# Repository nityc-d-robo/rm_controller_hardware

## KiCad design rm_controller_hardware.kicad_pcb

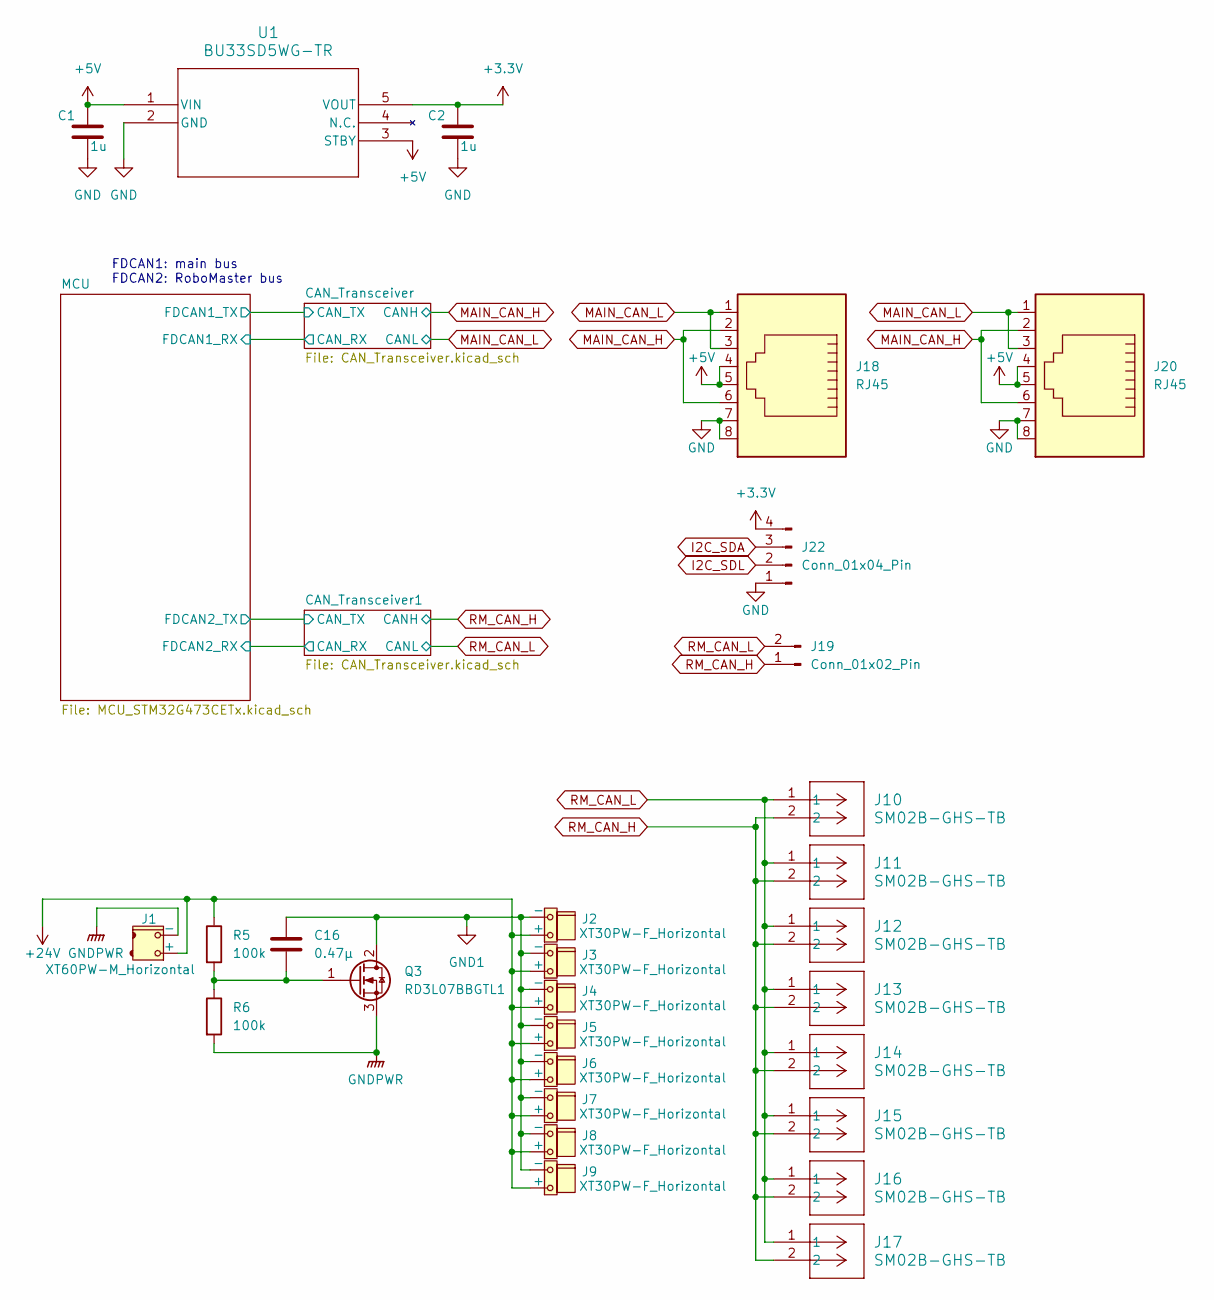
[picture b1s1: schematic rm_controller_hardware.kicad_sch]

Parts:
C1, C2: 1u; C_0603_1608Metric
C16: 0.47μ; C_0603_1608Metric_Pad1.08x0.95mm_HandSolder
J1: XT60PW-M_Horizontal; AMASS_XT60PW-M_1x02_P7.20mm_Horizontal
J2, J3, J4, J5, J6, J7, J8, J9: XT30PW-F_Horizontal; AMASS_XT30PW-F_1x02_P2.50mm_Horizontal
J10, J11, J12, J13, J14, J15, J16, J17: SM02B-GHS-TB; JST_GH_SM02B-GHS-TB_1x02-1MP_P1.25mm_Horizontal
J18, J20: RJ45; RJ45_Amphenol_54602-x08_Horizontal
J19: Conn_01x02_Pin; JST_XH_B2B-XH-A_1x02_P2.50mm_Vertical
J22: Conn_01x04_Pin; JST_XH_S4B-XH-A_1x04_P2.50mm_Horizontal
Q3: RD3L07BBGTL1; TO252-3_ROM
R5, R6: 100k; R_0603_1608Metric_Pad0.98x0.95mm_HandSolder
U1: BU33SD5WG-TR; SSOP5_ROM

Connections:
+5V: C1.1, J18.4, J18.5, J20.4, J20.5, U1.1 (VIN), U1.3 (STBY); also elsewhere on the board
+24V: J1.2 (+), J2.2 (+), J3.2 (+), J4.2 (+), J5.2 (+), J6.2 (+), J7.2 (+), J8.2 (+), J9.2 (+), R5.1
GND1: C16.1, J2.1 (-), J3.1 (-), J4.1 (-), J5.1 (-), J6.1 (-), J7.1 (-), J8.1 (-), J9.1 (-), Q3.2 (D)
GNDPWR: J1.1 (-), Q3.3 (S), R6.2
I2C_SDA: J22.3; also elsewhere on the board
I2C_SDL: J22.2; also elsewhere on the board
MAIN_CAN_H: J18.2, J18.6, J20.2, J20.6; also elsewhere on the board
MAIN_CAN_L: J18.1, J18.3, J20.1, J20.3; also elsewhere on the board
unnamed: C16.2, Q3.1 (G), R5.2, R6.1
RM_CAN_H: J10.2, J11.2, J12.2, J13.2, J14.2, J15.2, J16.2, J17.2, J19.1; also elsewhere on the board
RM_CAN_L: J10.1, J11.1, J12.1, J13.1, J14.1, J15.1, J16.1, J17.1, J19.2; also elsewhere on the board
VDD: C2.1, J22.4, U1.5 (VOUT); also elsewhere on the board
VSS: C1.2, C2.2, J18.7, J18.8, J20.7, J20.8, J22.1, U1.2 (GND); also elsewhere on the board

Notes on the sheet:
FDCAN1: main bus FDCAN2: RoboMaster bus

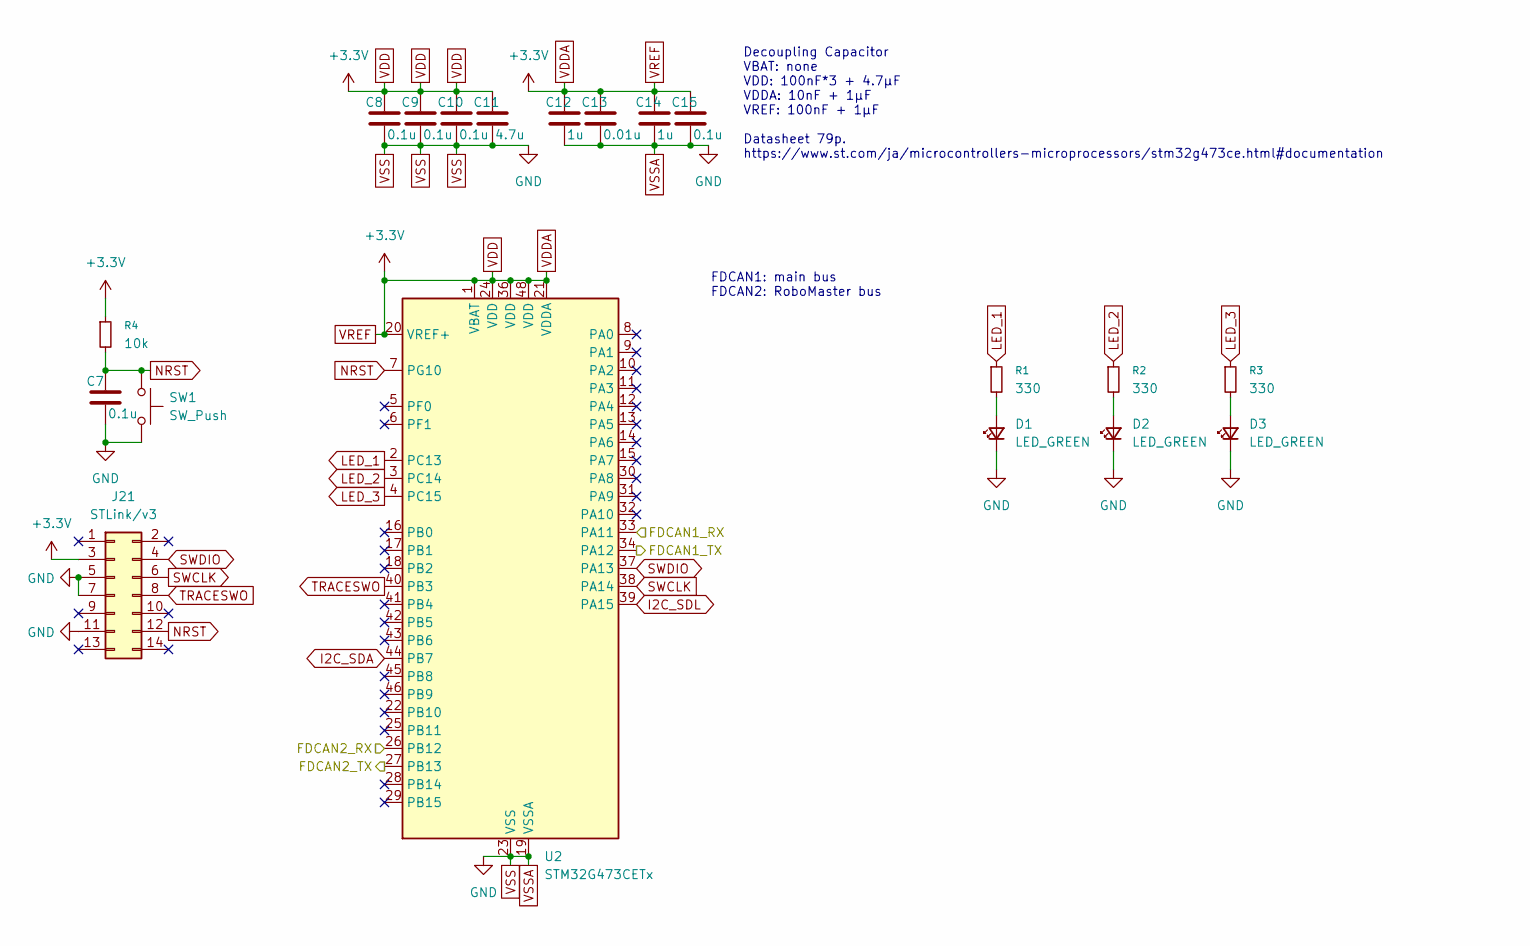
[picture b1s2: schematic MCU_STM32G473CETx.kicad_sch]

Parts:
C7, C8, C9, C10, C15: 0.1u; C_0603_1608Metric
C11: 4.7u; C_0603_1608Metric
C12, C14: 1u; C_0603_1608Metric
C13: 0.01u; C_0603_1608Metric
D1, D2, D3: LED_GREEN; LED_0603_1608Metric_Pad1.05x0.95mm_HandSolder
J21: STLink/v3; CONN14_3220-14_CNC
R1, R2, R3: 330; R_0603_1608Metric_Pad0.98x0.95mm_HandSolder
R4: 10k; R_0603_1608Metric_Pad0.98x0.95mm_HandSolder
SW1: SW_Push; TVAF06-A020B-R
U2: STM32G473CETx; LQFP-48_7x7mm_P0.5mm

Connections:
/CAN_Transceiver1/CAN_RX: U2.26 (PB12); also elsewhere on the board
/CAN_Transceiver1/CAN_TX: U2.27 (PB13); also elsewhere on the board
/CAN_Transceiver/CAN_RX: U2.33 (PA11); also elsewhere on the board
/CAN_Transceiver/CAN_TX: U2.34 (PA12); also elsewhere on the board
I2C_SDA: U2.44 (PB7); also elsewhere on the board
I2C_SDL: U2.39 (PA15); also elsewhere on the board
LED_1: R1.1, U2.2 (PC13)
LED_2: R2.1, U2.3 (PC14)
LED_3: R3.1, U2.4 (PC15)
NRST: C7.1, J21.12, R4.2, SW1.1, U2.7 (PG10)
unnamed: D1.2 (A), R1.2
unnamed: D2.2 (A), R2.2
unnamed: D3.2 (A), R3.2
SWCLK: J21.6, U2.38 (PA14)
SWDIO: J21.4, U2.37 (PA13)
TRACESWO: J21.8, U2.40 (PB3)
VDD: C8.1, C9.1, C10.1, C11.1, C12.1, C13.1, C14.1, C15.1, J21.3, R4.1, U2.1 (VBAT), U2.20 (VREF+), U2.21 (VDDA), U2.24 (VDD), U2.36 (VDD), U2.48 (VDD); also elsewhere on the board
VSS: C7.2, C8.2, C9.2, C10.2, C11.2, C12.2, C13.2, C14.2, C15.2, D1.1 (K), D2.1 (K), D3.1 (K), J21.5, J21.7, J21.11, SW1.2, U2.19 (VSSA), U2.23 (VSS), U2.35 (VSS), U2.47 (VSS); also elsewhere on the board

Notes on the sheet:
FDCAN1: main bus FDCAN2: RoboMaster bus
Decoupling Capacitor VBAT: none VDD: 100nF*3 + 4.7μF VDDA: 10nF + 1μF VREF: 100nF + 1μF Datasheet 79p. https://www.st.com/ja/microcontrollers-microprocessors/stm32g473ce.html#documentation

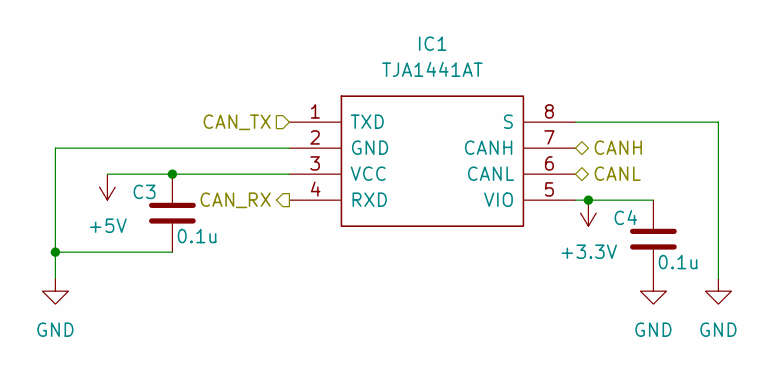
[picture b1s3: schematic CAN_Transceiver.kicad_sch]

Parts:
C3, C4: 0.1u; C_0603_1608Metric_Pad1.08x0.95mm_HandSolder
IC1: TJA1441AT; SO8_SOT96-1_NXP; Manufacturer_Part_Number TJA1441AT

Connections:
+5V: C3.1, IC1.3 (VCC); also elsewhere on the board
/CAN_Transceiver1/CAN_RX: IC1.4 (RXD); also elsewhere on the board
/CAN_Transceiver1/CAN_TX: IC1.1 (TXD); also elsewhere on the board
RM_CAN_H: IC1.7 (CANH); also elsewhere on the board
RM_CAN_L: IC1.6 (CANL); also elsewhere on the board
VDD: C4.1, IC1.5 (VIO); also elsewhere on the board
VSS: C3.2, C4.2, IC1.2 (GND), IC1.8 (S); also elsewhere on the board

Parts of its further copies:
C5, C6: 0.1u; C_0603_1608Metric_Pad1.08x0.95mm_HandSolder
IC2: TJA1441AT; SO8_SOT96-1_NXP; Manufacturer_Part_Number TJA1441AT

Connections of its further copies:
+5V: C5.1, IC2.3 (VCC); also elsewhere on the board
/CAN_Transceiver/CAN_RX: IC2.4 (RXD); also elsewhere on the board
/CAN_Transceiver/CAN_TX: IC2.1 (TXD); also elsewhere on the board
MAIN_CAN_H: IC2.7 (CANH); also elsewhere on the board
MAIN_CAN_L: IC2.6 (CANL); also elsewhere on the board
VDD: C6.1, IC2.5 (VIO); also elsewhere on the board
VSS: C5.2, C6.2, IC2.2 (GND), IC2.8 (S); also elsewhere on the board

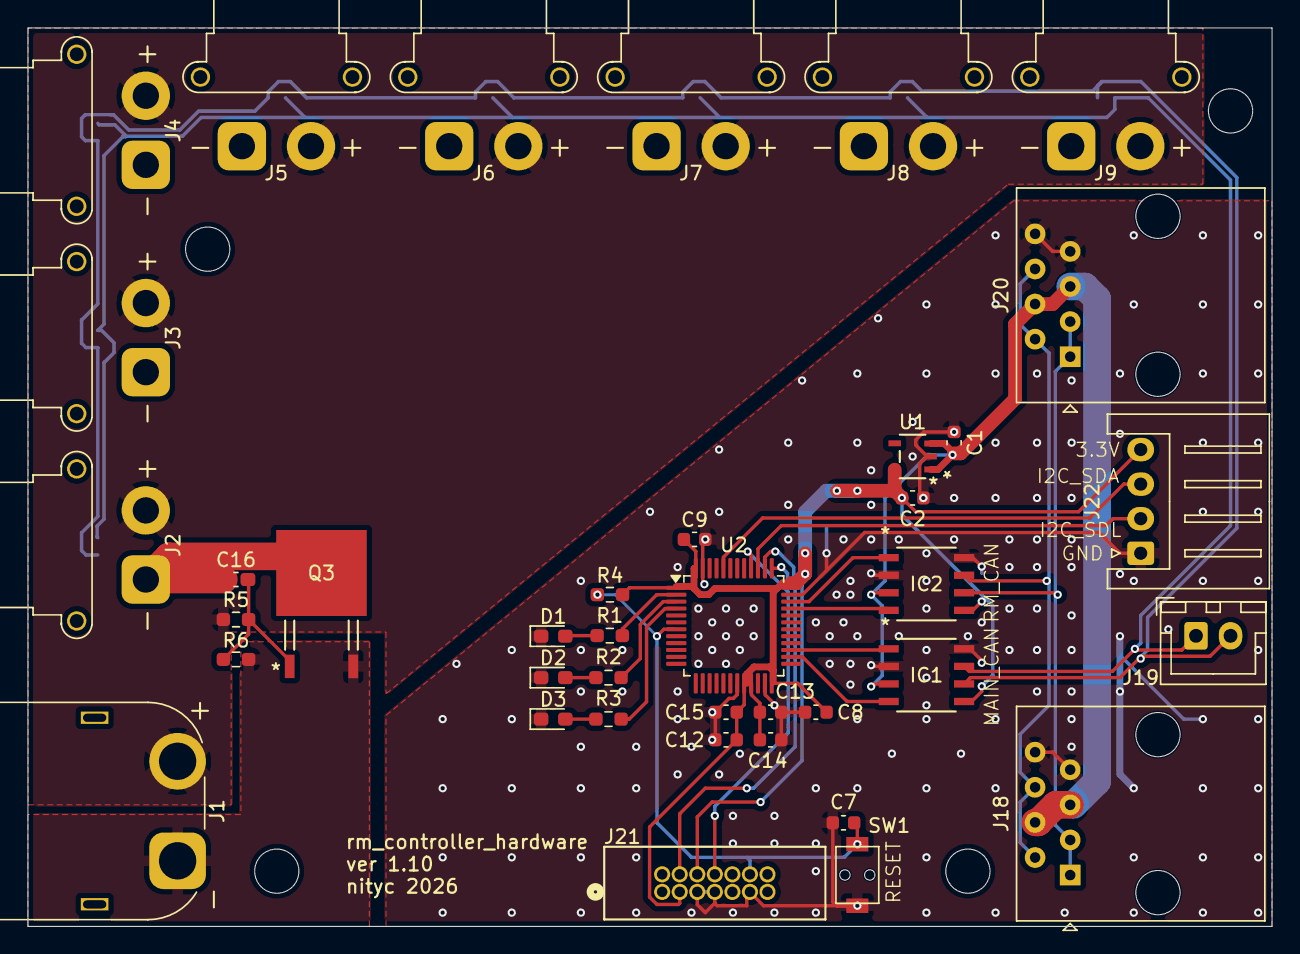
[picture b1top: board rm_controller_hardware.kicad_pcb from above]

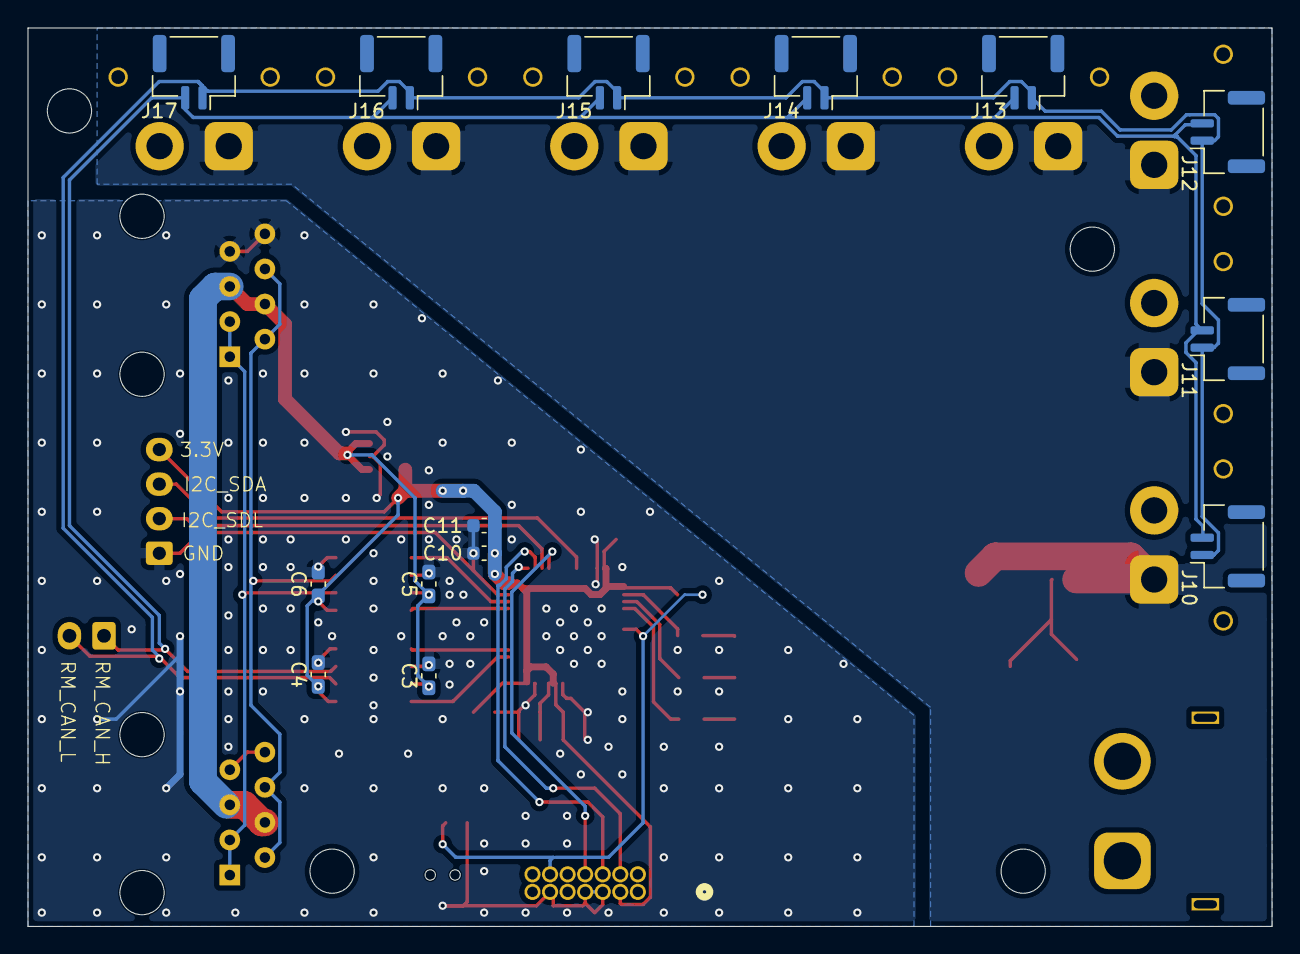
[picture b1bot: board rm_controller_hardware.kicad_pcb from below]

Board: 2 copper layers, 90.0 x 65.0 mm, 53 parts (14 on the bottom side), 27 nets.

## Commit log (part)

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2025-09-25 add .gitignore
2025-09-25 apply .gitignore
2026-02-22 ver1.00
